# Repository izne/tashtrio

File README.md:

# TashTrio

Firmware that emulates a trio of devices for Apple's ADB bus: a keyboard, a mouse, and a Global Village TelePort A300 ADB modem.  The emulated keyboard and mouse are controlled by a PS/2 keyboard and mouse, the emulated modem is connected to a two-wire UART.

## Special Keys

The menu key on the PS/2 keyboard is used as a modifier key which can be held and combined with the following keys:

| Key   | Function                       |
| ----- | ------------------------------ |
| F1    | Change UART baud rate to 300.  |
| F2    | Change UART baud rate to 1200. |
| F3    | Change UART baud rate to 2400. |
| F4    | Change UART baud rate to 4800.  Note that this may cause the device connected to the UART to send faster than the Macintosh can receive, which will result in undefined behavior. |
| Pause | Send power key keypress.  Note that this cannot be used to start up the Macintosh, as the microcontroller requires power to be able to read the PS/2 keyboard. |

## Caveats

PS/2 mice require their host to send a command byte to start the flow of mouse movement data.  TashTrio firmware sends this byte on startup only, meaning that the PS/2 mouse must be plugged in at powerup time or it will appear dead.  Because some newer Macintosh computers are known to supply power to the ADB port even when powered down, it is necessary to connect the PS/2 mouse before connecting to the ADB.

## Building Firmware

Building the firmware requires Microchip MPASM, which is included with their development environment, MPLAB.  Note that you **must** use MPLAB X version 5.35 or earlier or MPLAB 8 as later versions of MPLAB X have removed MPASM.

### Download links

[MPLAB Archives](https://www.microchip.com/en-us/tools-resources/archives/mplab-ecosystem)

[MPLABX-v5.35-windows](https://ww1.microchip.com/downloads/en/DeviceDoc/MPLABX-v5.35-windows-installer.exe)

## PS2toADB board
Just a quick, minimal schematic.

## Writing the firmware to the PIC12
[ICSP LVP with just an FT232R adapter](https://github.com/izne/PIC12-LVP-FTDI) appears to be one fast and cheap way. 

## Info on LVP limitations
There are certain limitations on PIC12F1840 when programmed the LVP way. In this method, the MCLR pin must remain MCLR and cannot take GPIO functions. Therefore, RA3 cannot be used if the firmware is programmed in LVP mode.
RA3 is the PS/2 Keyboard Data signal, therefore the keyboard will not work if the firmware is programmed in LVP mode. 
When firmware is programmed in HVP mode (like with PICkit3), the RA3 pin can take GPIO function and the keyboard will work.

## PS/2 Keyboard workaround for LVP
RA1 (UART RX) can be used instead of RA3 for PS2 keyboard data input. Switching between RA1 and RA3 could be implemented via 2-pole switch or jumper on the board.

## PICPgm on Windows
One option on Windows is PICPgm. For FT232R, you need to use the USB LVP programmer preset and remap the pins.
Attached a one-pager PICPgm hints for FT23.

## References
[Microchip PIC12F1840 Product page](https://www.microchip.com/en-us/product/pic12f1840)

[Microchip PIC12F1840 Datasheet](https://ww1.microchip.com/downloads/en/DeviceDoc/41441B.pdf)

[8-bit PIC design recommendations](https://developerhelp.microchip.com/xwiki/bin/view/products/mcu-mpu/8bit-pic/design-recommendations/)

[PICPgm with FT232 adapter](https://www.franksteinberg.de/FT232-PIC-Programmer.htm)

[TMK ADB Keyboard](https://github.com/tmk/tmk_keyboard/wiki/Apple-Desktop-Bus)

[Topic: TMK ADB to USB keyboard converter](https://geekhack.org/index.php?topic=14290.msg277407#msg277407)

[Microchip Application Note AN591 - Apple® Desktop Bus](https://ww1.microchip.com/downloads/en/AppNotes/00591b.pdf)

[PIC12F1840 Programming](https://www.northernsoftware.com/dev/pic12f/pic12f1840.htm)

[PIC12F1840 HVP Circuit](https://www.northernsoftware.com/nsdsp/hvp.htm)

[Microchip Application Note 589 - HVP parallel programmer](https://ww1.microchip.com/downloads/en/appnotes/00589a.pdf)

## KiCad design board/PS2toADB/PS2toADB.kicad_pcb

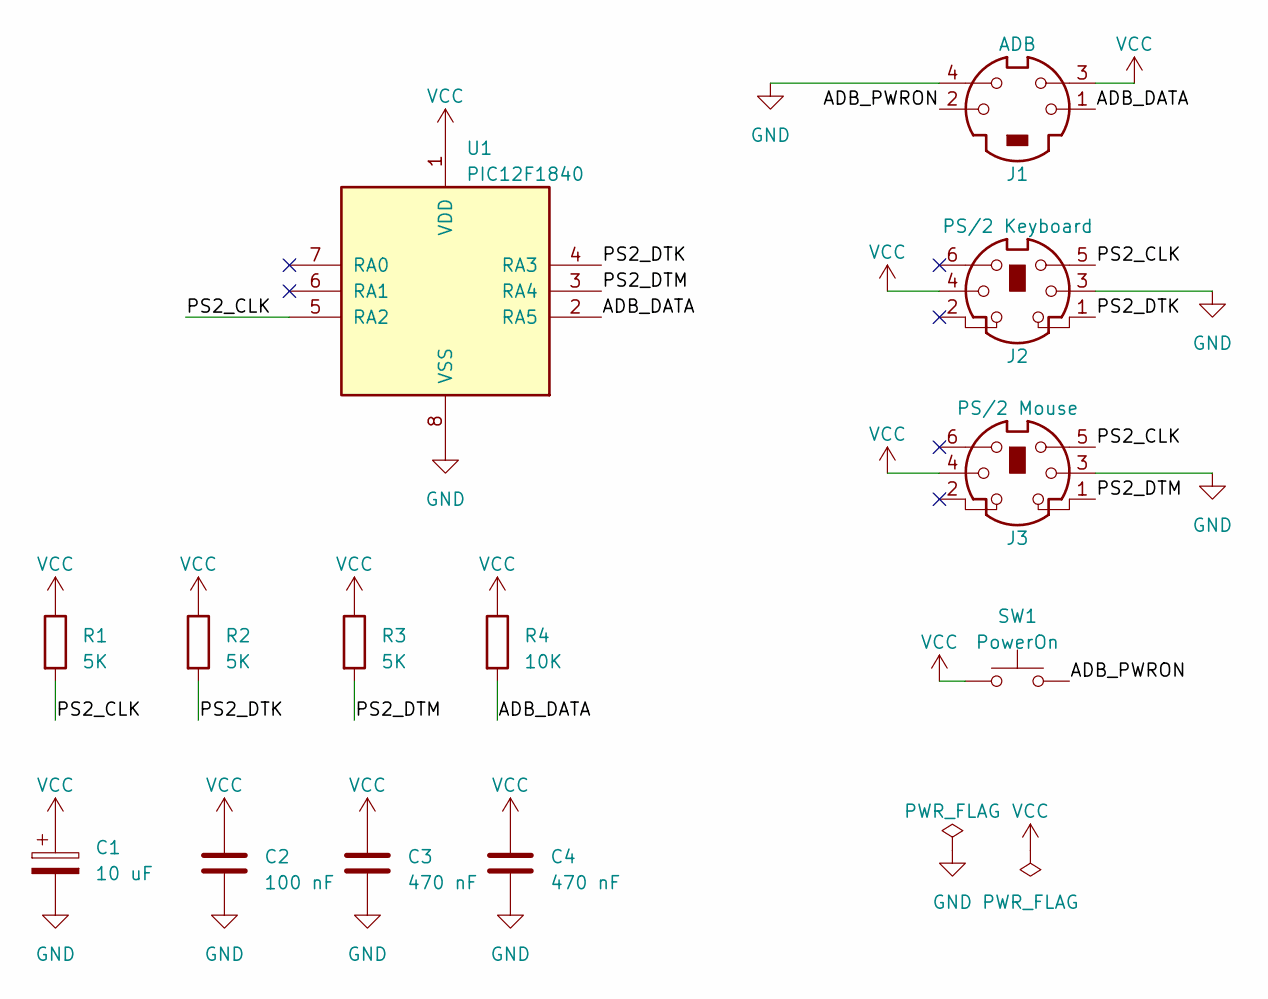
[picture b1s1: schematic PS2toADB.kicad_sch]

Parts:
C1: 10 uF; CP_Radial_D5.0mm_P2.00mm
C2: 100 nF; C_Disc_D3.0mm_W1.6mm_P2.50mm
C3, C4: 470 nF; C_Disc_D3.0mm_W1.6mm_P2.50mm
J1: ADB; MINI-DIN-4-FULL-SHIELD
J2: PS/2 Keyboard; MINI-DIN-6-FULL-SHIELD
J3: PS/2 Mouse; MINI-DIN-6-FULL-SHIELD
R1, R2, R3: 5K; R_Axial_DIN0204_L3.6mm_D1.6mm_P2.54mm_Vertical
R4: 10K; R_Axial_DIN0204_L3.6mm_D1.6mm_P2.54mm_Vertical
SW1: PowerOn; SW_PUSH_6mm_H5mm
U1: PIC12F1840; DIP-8_W7.62mm

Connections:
/ADB_DATA: J1.1, R4.2, U1.2 (RA5)
/ADB_PWRON: J1.2, SW1.2
/PS2_CLK: J2.5, J3.5, R1.2, U1.5 (RA2)
/PS2_DTK: J2.1, R2.2, U1.4 (RA3)
/PS2_DTM: J3.1, R3.2, U1.3 (RA4)
GND: C1.2, C2.2, C3.2, C4.2, J1.4, J2.3, J3.3, U1.8 (VSS)
VCC: C1.1, C2.1, C3.1, C4.1, J1.3, J2.4, J3.4, R1.1, R2.1, R3.1, R4.1, SW1.1, U1.1 (VDD)

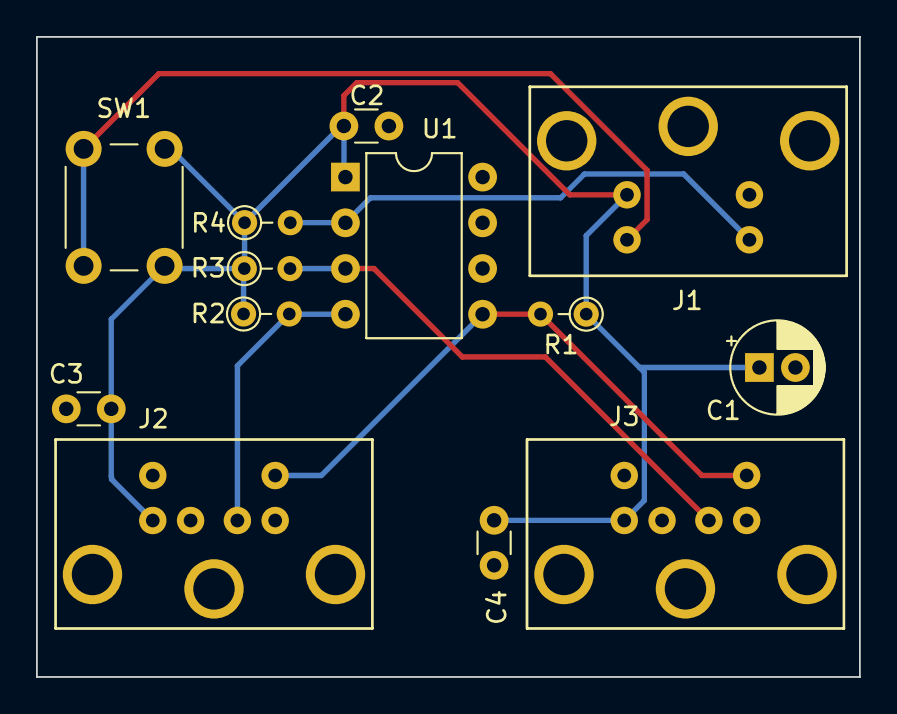
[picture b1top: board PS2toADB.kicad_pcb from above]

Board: 2 copper layers, 45.7 x 35.6 mm, 13 parts (0 on the bottom side), 7 nets.

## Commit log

2024-02-10 First board iteration
2024-02-10 Images, Docs update, Datasheets added
2024-02-15 Programming the PIC
2024-02-16 Docs update
2024-03-15 Keyboard updates on docs
2024-03-15 Doc upd1
2024-03-30 Updated schematic. Added power button and renders
2024-03-30 Added link to PIC12-LVP-FTDI programmer
